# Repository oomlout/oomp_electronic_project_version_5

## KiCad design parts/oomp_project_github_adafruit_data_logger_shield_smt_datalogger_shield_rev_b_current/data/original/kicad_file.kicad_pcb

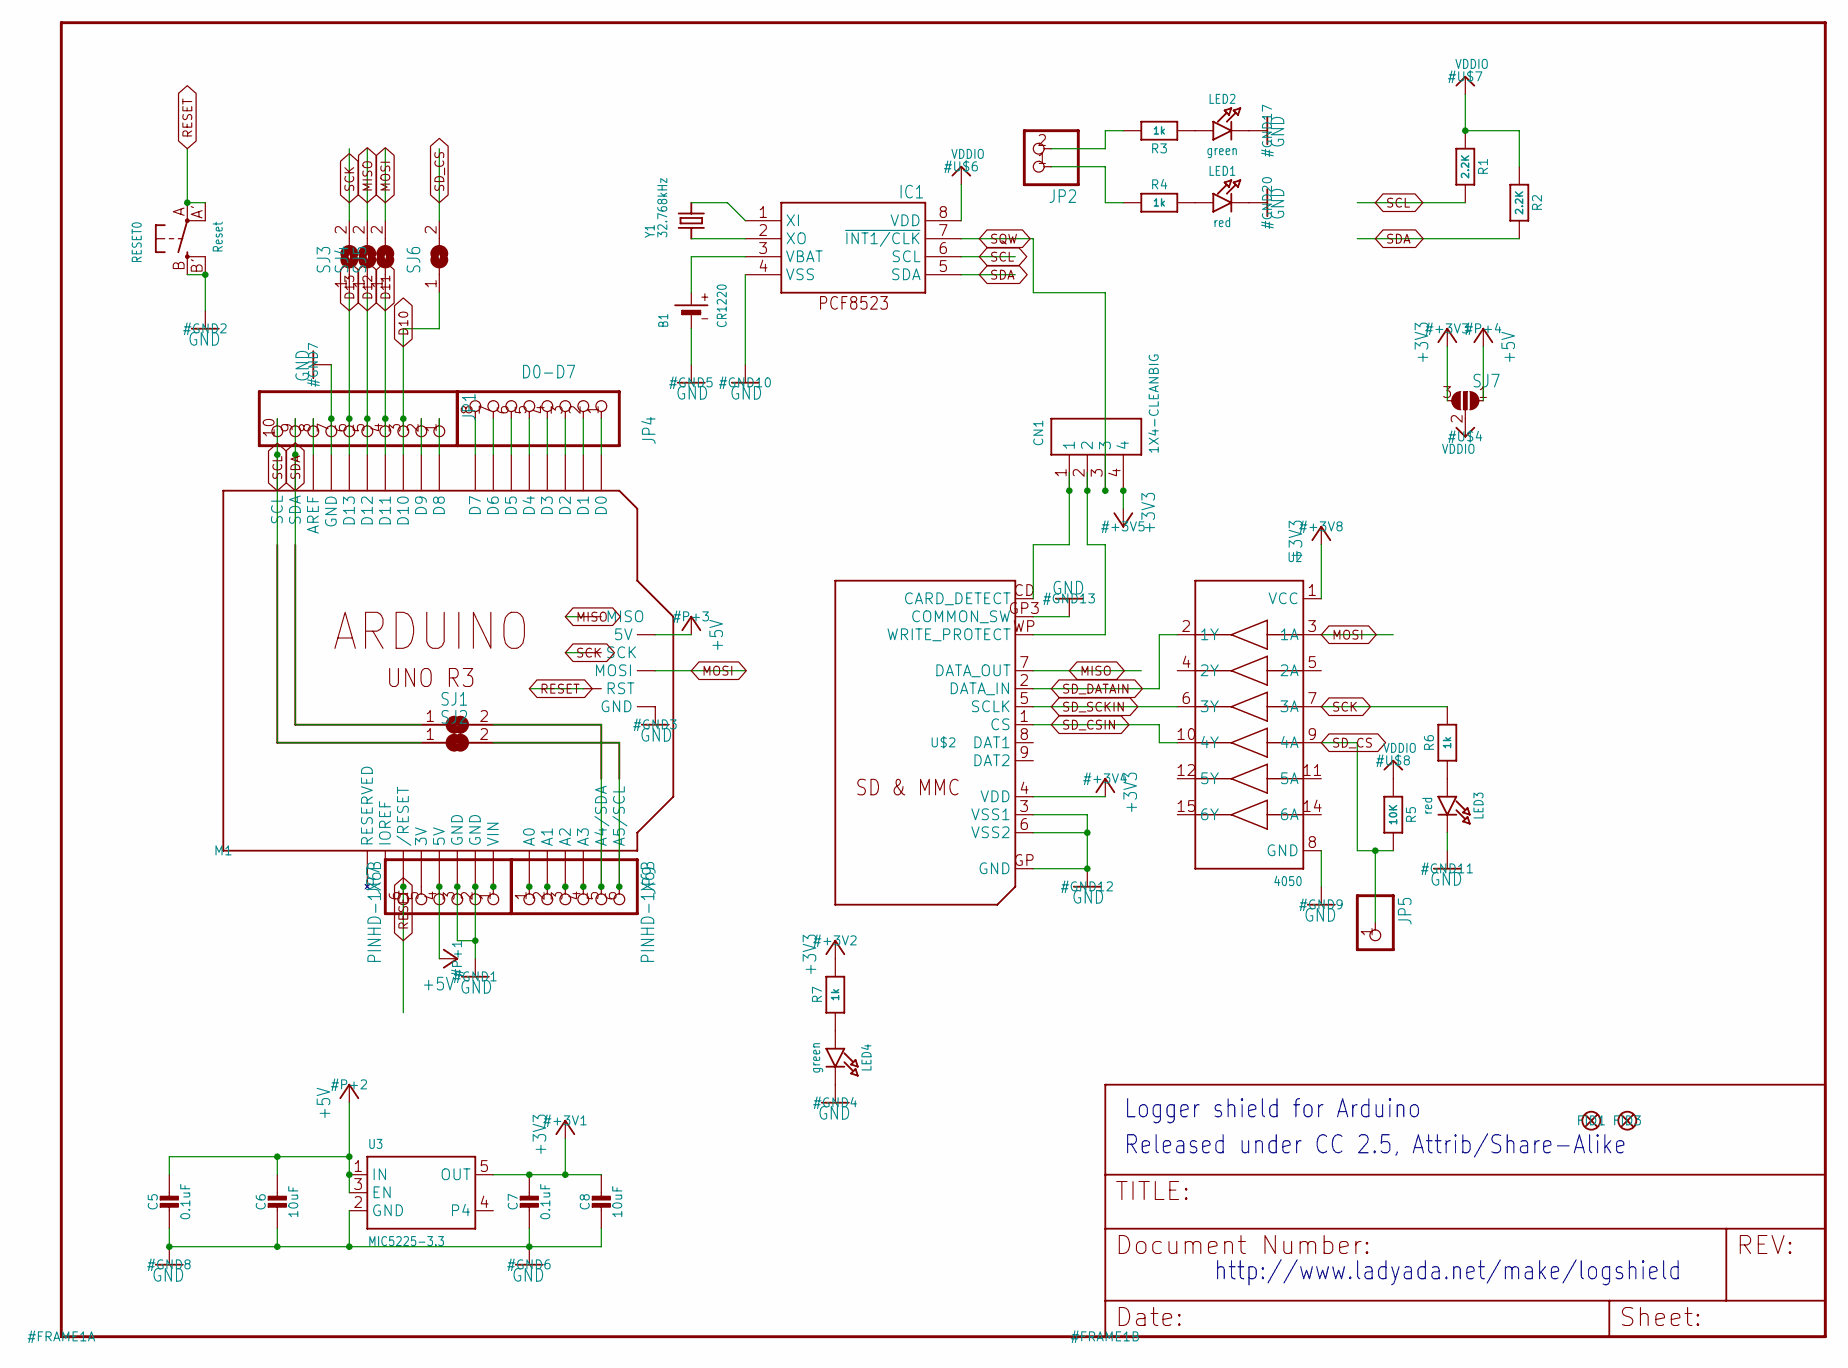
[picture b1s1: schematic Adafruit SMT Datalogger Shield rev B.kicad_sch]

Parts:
B1: CR1220
C5, C7: 0.1uF; 0805-NO
C6, C8: 10uF; 0805-NO
CN1: 1X4-CLEANBIG; 1X04-CLEANBIG
FID1, FID3: FIDUCIAL""; FIDUCIAL_1MM
IC1: RTC_PCF8523T; SOIC8_150MIL
JP1: HEADER-1X1070MIL; 1X10_ROUND70
JP2: HEADER-1X2ROUND; 1X02_ROUND
JP4: D0-D7; 1X08-BIG
JP5: HEADER-1X1ROUND; 1X01_ROUND
JP7, JP9: PINHD-1X6B; 1X06-BIG
LED1, LED3: red; CHIPLED_0805_NOOUTLINE
LED2, LED4: green; CHIPLED_0805_NOOUTLINE
M1: ARDUINO_R3_ICSP; ARDUINOR3_ICSP
R1, R2: 2.2K; 0805-NO
R3, R4, R6, R7: 1k; 0805-NO
R5: 10K; 0805-NO
RESET0: Reset; EVQ-Q2
SJ1, SJ2, SJ3, SJ4, SJ5: SOLDERJUMPER; SOLDERJUMPER_ARROW_NOPASTE
SJ6: SOLDERJUMPERCLOSED; SOLDERJUMPER_CLOSEDWIRE
SJ7: SOLDERJUMPER_2WAY; SOLDERJUMPER_2WAY_OPEN_NOPASTE
U2: 4050; SOIC16
U3: MIC5225-3.3; SOT23-5
U$2: SDMMC06132; 06132
Y1: 32.768kHz; CRYSTAL_8X3.8

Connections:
3.3V: JP7.5, M1.3V
+3V3: C7.1, C8.1, CN1.4, R7.2, SJ7.3, U2.1 (VCC), U3.5 (OUT), U$2.4 (VDD)
+5V: C5.1, C6.1, JP7.4, M1.5V, M1.5V_ICSP (5V), SJ7.1, U3.1 (IN), U3.3 (EN)
A4: JP9.5, M1.A4 (A4/SDA), SJ1.2
A5: JP9.6, M1.A5 (A5/SCL), SJ2.2
D10: JP1.3, M1.D10, SJ6.1
D11: JP1.4, M1.D11, SJ5.1
D12: JP1.5, M1.D12, SJ4.1
D13: JP1.6, M1.D13, SJ3.1
GND: B1.-, C5.2, C6.2, C7.2, C8.2, IC1.4 (VSS), JP1.7, JP7.2, JP7.3, LED1.C, LED2.C, LED3.C, LED4.C, M1.GND, M1.GND@1 (GND), M1.GND@2 (GND), M1.GND@3 (GND), RESET0.B (S), RESET0.B' (S1), U2.8 (GND), U3.2 (GND), U$2.3 (VSS1), U$2.6 (VSS2), U$2.GP (GND), U$2.GP3 (COMMON_SW)
MISO: M1.MISO, SJ4.2, U$2.7 (DATA_OUT)
MOSI: M1.MOSI, SJ5.2, U2.3 (1A)
unnamed: LED1.A, R4.2
unnamed: IC1.2 (XO), Y1.P$1 (1)
unnamed: IC1.1 (XI), Y1.P$4 (2)
unnamed: LED2.A, R3.1
unnamed: LED3.A, R6.1
unnamed: JP7.1, M1.VIN
unnamed: JP2.2, R3.2
unnamed: JP2.1, R4.1
unnamed: JP4.1, M1.D0
unnamed: JP4.2, M1.D1
unnamed: JP4.3, M1.D2
unnamed: JP4.4, M1.D3
unnamed: JP4.5, M1.D4
unnamed: JP4.6, M1.D5
unnamed: JP4.7, M1.D6
unnamed: JP4.8, M1.D7
unnamed: JP1.8, M1.AREF
unnamed: JP1.2, M1.D9
unnamed: JP1.1, M1.D8
unnamed: LED4.A, R7.1
unnamed: JP9.1, M1.A0
unnamed: JP9.2, M1.A1
unnamed: JP9.3, M1.A2
unnamed: JP9.4, M1.A3
RESET: JP7.6, M1.RESET (/RESET), M1.RESET_ICSP (RST), RESET0.A, RESET0.A' (P1)
SCK: M1.SCK, R6.2, SJ3.2, U2.7 (3A)
SCL: IC1.6 (SCL), JP1.10, M1.SCL, R1.2, SJ2.1
SDA: IC1.5 (SDA), JP1.9, M1.SDA, R2.2, SJ1.1
SD_CD: CN1.1, U$2.CD (CARD_DETECT)
SD_CS: JP5.1, R5.2, SJ6.2, U2.9 (4A)
SD_CSIN: U2.10 (4Y), U$2.1 (CS)
SD_DATAIN: U2.2 (1Y), U$2.2 (DATA_IN)
SD_SCKIN: U2.6 (3Y), U$2.5 (SCLK)
SD_WP: CN1.2, U$2.WP (WRITE_PROTECT)
SQW: CN1.3, IC1.7 (~INT1/CLK)
VBAT: B1.+$1 (+), IC1.3 (VBAT)
VDDIO: IC1.8 (VDD), R1.1, R2.1, R5.1, SJ7.2

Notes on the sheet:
http://www.ladyada.net/make/logshield
Released under CC 2.5, Attrib/Share-Alike
Logger shield for Arduino

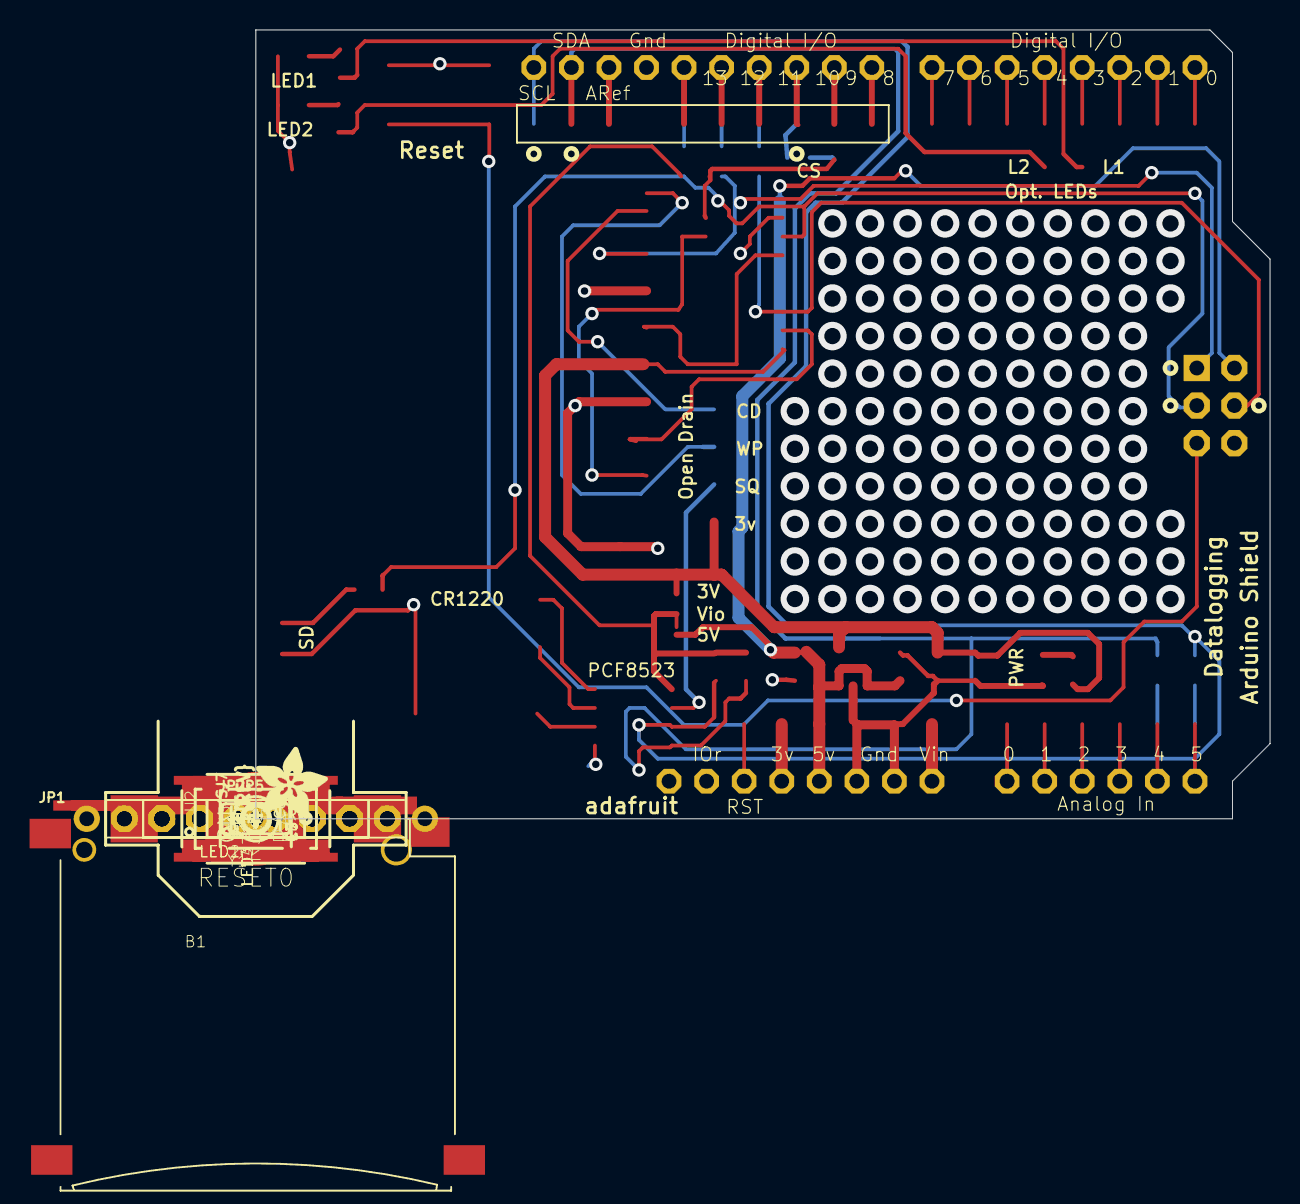
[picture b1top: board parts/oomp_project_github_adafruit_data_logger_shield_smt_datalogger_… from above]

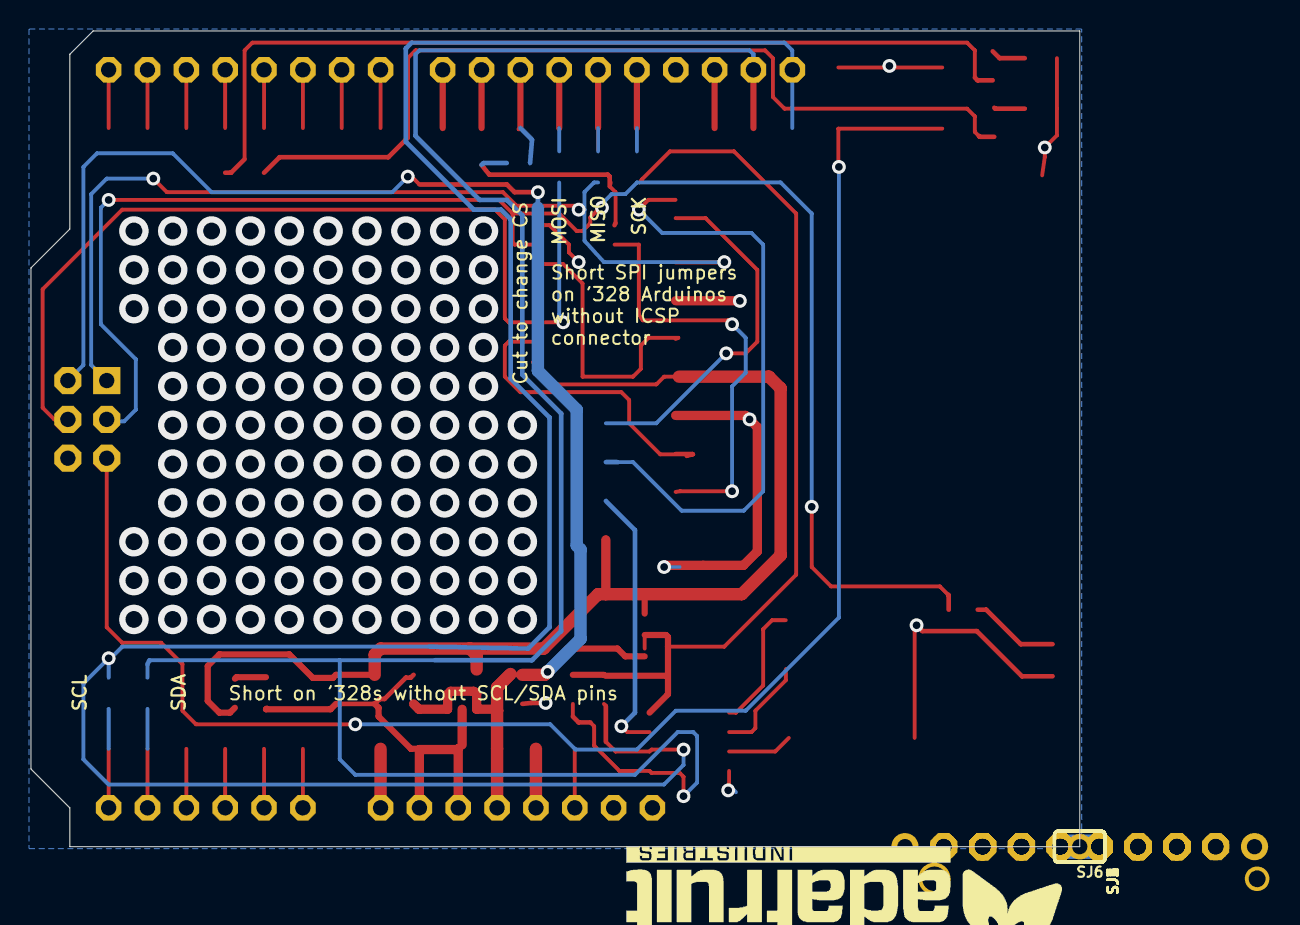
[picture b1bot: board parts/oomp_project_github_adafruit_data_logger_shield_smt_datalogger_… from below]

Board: 2 copper layers, 68.6 x 53.3 mm, 42 parts (7 on the bottom side), 49 nets.

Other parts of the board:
U$1: ADAFRUIT_TEXT_30MM
U$3: PCBFEAT-REV-040
U$5: ADAFRUIT_5MM

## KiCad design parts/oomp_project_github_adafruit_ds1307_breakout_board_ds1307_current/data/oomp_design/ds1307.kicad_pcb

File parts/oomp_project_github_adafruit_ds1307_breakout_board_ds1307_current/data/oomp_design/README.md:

# OOMP KiCad design copy

Open `ds1307.kicad_pro` (or the `.kicad_pcb` / `.kicad_sch`) in KiCad. Local OOMP libraries are under `libraries/`. Original inputs are preserved in [../original/](../original/).

Only verified unchanged installed KiCad defaults were renamed. Modified, custom, unmatched and unavailable items remain unchanged. Soldering variants are never swapped during conversion. Existing pad coordinates, nets and UUIDs are preserved.

See [conversion_report.yaml](conversion_report.yaml) for every conversion and skip. Copy this directory before editing; regeneration refuses to overwrite edited design files.

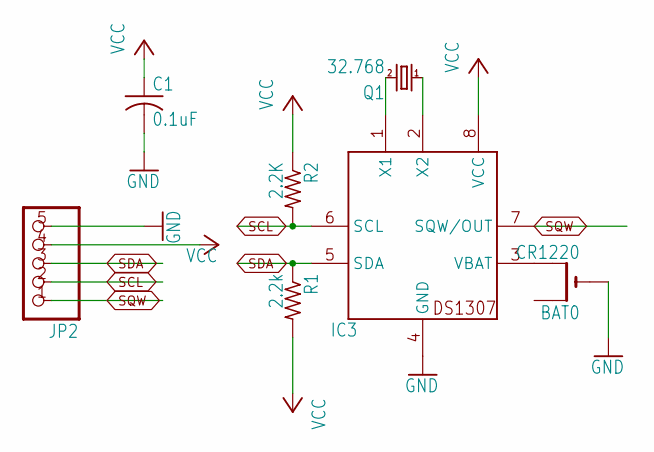
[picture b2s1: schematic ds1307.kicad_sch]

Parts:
BAT0: CR1220; CR1220-THM
C1: 0.1uF; C025-025X050
IC3: DS1307; DIL08
JP2: PINHD-1X5; 1X05
Q1: 32.768; TC38H
R1: 2.2k; 0207_10
R2: 2.2K; 0207_10

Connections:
GND: BAT0.-, C1.2, IC3.4 (GND), JP2.5
unnamed: IC3.1 (X1), Q1.2
unnamed: IC3.2 (X2), Q1.1
unnamed: BAT0.+2 (+1), IC3.3 (VBAT)
SCL: IC3.6 (SCL), JP2.2, R2.2
SDA: IC3.5 (SDA), JP2.3, R1.1
SQW: IC3.7 (SQW/OUT), JP2.1
VCC: C1.1, IC3.8 (VCC), JP2.4, R1.2, R2.1

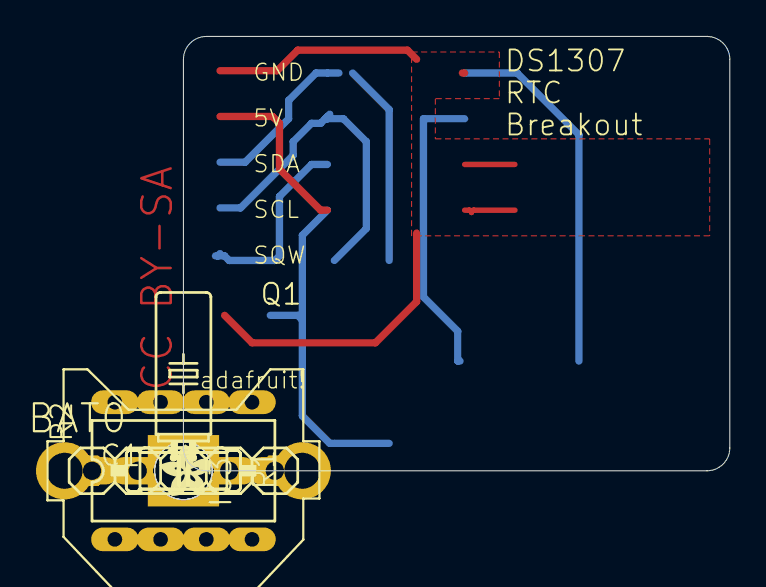
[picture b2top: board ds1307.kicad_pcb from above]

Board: 16 copper layers, 30.4 x 24.1 mm, 10 parts (0 on the bottom side), 8 nets.

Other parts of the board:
U$1: ADAFRUIT200MIL
UNK_HOLE_0: dummyfp0
UNK_HOLE_1: dummyfp1

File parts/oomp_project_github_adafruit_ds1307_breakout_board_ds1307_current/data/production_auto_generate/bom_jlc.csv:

Comment,Designator,Footprint,LCSC Part #
,JP2,ds1307-import-fps:1X05,C42431835
,U$1,ds1307-import-fps:ADAFRUIT200MIL,
0.1uF,C1,ds1307-import-fps:C025-025X050,
2.2k,R1,ds1307-import-fps:0207_10,
2.2K,R2,ds1307-import-fps:0207_10,
32.768,Q1,ds1307-import-fps:TC38H,
CR1220,BAT0,ds1307-import-fps:CR1220-THM,
DS1307,IC3,ds1307-import-fps:DIL08,

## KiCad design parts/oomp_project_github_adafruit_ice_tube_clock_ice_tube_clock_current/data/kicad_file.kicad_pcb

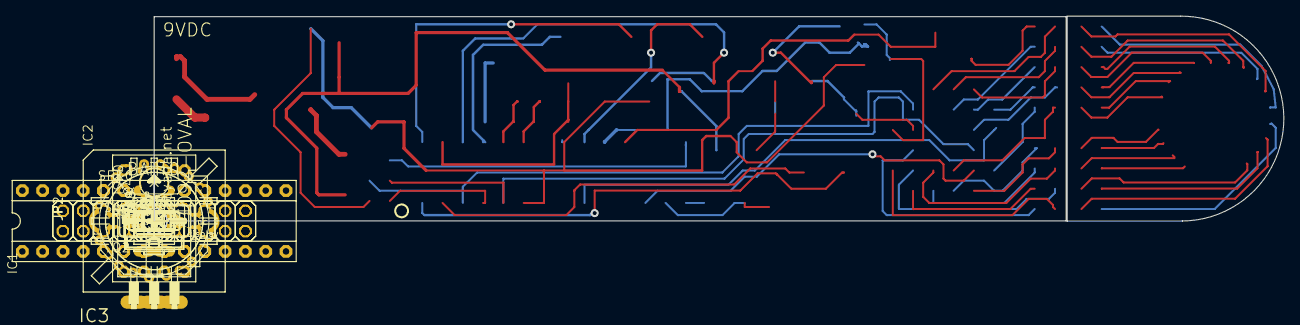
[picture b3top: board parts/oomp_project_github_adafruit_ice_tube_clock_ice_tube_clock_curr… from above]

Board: 16 copper layers, 141.5 x 25.7 mm, 33 parts (0 on the bottom side), 7 nets.

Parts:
BATT0: CR1220; CR1220-THM
C7: 47uF/25V; E2,5-6
C8, C9: 22pf; C025-025X050
C10: 0.1uF; C025-024X044
CT0, CT1: 1X01
D2, D4: 1N5817; DO41-10
D5: 60V zener; DO41Z10
DIS1: IV18
F1: FUSETE5; TE5
IC1: ATMEGA168V; DIL28_3
IC2: MAX6921; PLCC-S28
IC3: 7805T; TO220H
ISP0: ISP; 2X03
JP1: female; 2X10
JP2: male; 2X10
Q1: 32.768 khz; TC26V
Q2: IRFD110; DIL04
Q4: PFETZVP3306; ladyada.net
R1: 270k; 0207_10
R2: 100k; 0207_10
R3: 22; 0207_10
R4: 1.0 K; 0207_5V
R5: 10k; 0207_5V
S1, S2, S3: B3F-31XX
SPK0: PS1240; PS12
SW1: ALARM; OS102011MA1Q
UNK_HOLE_0: dummyfp0
UNK_HOLE_1: dummyfp1

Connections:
+9V: C7.-, D5.C, DIS1.17, IC1.2, ISP0.2, R2.2
+UB: IC2.2, Q1.1, S1.2, S2.1
BATTSNS: JP2.2, S3.1
unnamed: DIS1.6, IC2.1, SW1.2, SW1.MT2
unnamed: BATT0.-, C9.1
unnamed: F1.1, R5.1
VCC: D4.C, JP1.2, JP2.1, R1.1, R3.2

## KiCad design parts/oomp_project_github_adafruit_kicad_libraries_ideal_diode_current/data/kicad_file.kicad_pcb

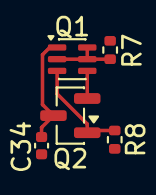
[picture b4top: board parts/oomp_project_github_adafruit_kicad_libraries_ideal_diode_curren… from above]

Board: 4 copper layers, 5 parts (0 on the bottom side), 5 nets.

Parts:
C34: 1uF/16V(10%); C_0402_1005Metric
Q1: MBT3906DW1; SOT-363_SC-70-6
Q2: AO3401A; SOT-23
R7: 10K(1%); R_0402_1005Metric
R8: 51K(1%); R_0402_1005Metric

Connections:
/FS_VBUS: C34.1, Q1.1 (E1), Q2.3 (D)
GND: C34.2, R7.2, R8.2
unnamed: Q1.2 (B1), Q1.5 (B2), Q1.6 (C1), R7.1
unnamed: Q1.3 (C2), Q2.1 (G), R8.1
VBUS: Q1.4 (E2), Q2.2 (S)

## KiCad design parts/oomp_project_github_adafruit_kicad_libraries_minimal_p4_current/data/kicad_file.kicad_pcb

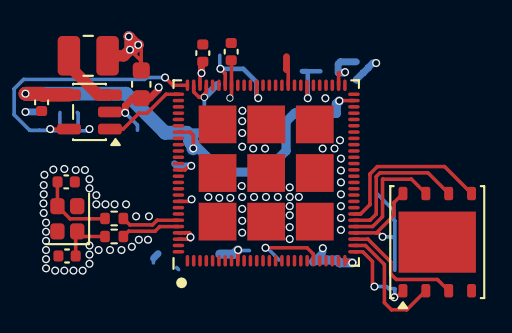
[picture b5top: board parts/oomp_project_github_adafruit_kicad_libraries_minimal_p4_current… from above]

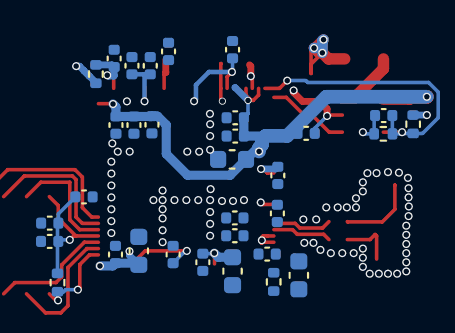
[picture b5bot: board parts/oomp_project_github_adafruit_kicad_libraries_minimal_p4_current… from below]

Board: 4 copper layers, 45 parts (32 on the bottom side), 20 nets.

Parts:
C1, C42: 4.7uF; C_0402_1005Metric
C2: 22pF; C_0402_1005Metric
C3: 22uF; C_0603_1608Metric
C4, C5: 12pF; C_0402_1005Metric
C6, C7, C8, C9, C12, C13, C15, C16, C21, C23, C24, C25, C26, C31, C32, C33, C40: 0.1uF; C_0402_1005Metric
C11, C14, C20, C28: 10uF; C_0603_1608Metric
C17, C18, C27, C29, C30: 1uF; C_0402_1005Metric
C41: 10nF; C_0402_1005Metric
L1: 2.2uH; L_1008_2520Metric
R1, R2: 499k; R_0402_1005Metric
R3, R4, R39: 0; R_0402_1005Metric
R28, R200: 10k; R_0402_1005Metric
U1: TLV62569DBV; SOT-23-5
U2: ESP32-P4
U3: W25Q128JVS; WSON-8-1EP_6x5mm_P1.27mm_EP3.4x4.3mm
Y1: 40MHz(+-10 ppm) C501798; Crystal_SMD_2016-4Pin_2.0x1.6mm

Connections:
+3.3V: C1.1, C6.1, C7.1, C9.1, C11.1, C12.1, C13.1, C14.1, C16.1, C20.1, C21.1, C23.1, C24.1, C40.1, C41.1, C42.1, R200.2, U1.4 (VIN), U2.9 (VDD_LP), U2.21 (VDD_IO_0), U2.51 (VDD_USBPHY), U2.62 (VDD_IO_4), U2.75 (VDD_LDO), U2.77 (VDD_DCDCC), U2.85 (VDD_IO_5), U2.96 (VDD_IO_6), U2.101 (VDD_ANA), U2.102 (VDD_BAT)
/Minimal P4 V3/EN_DCDC: U1.1 (EN), U2.79 (EN_DCDC)
/Minimal P4 V3/FB_DCDC: C2.2, R1.1, R2.2, U1.5 (FB), U2.78 (FB_DCDC)
/Minimal P4 V3/FLASH_CK: U2.32 (FLASH_CK), U3.6 (CLK)
/Minimal P4 V3/FLASH_CS: R28.1, U2.27 (FLASH_CS), U3.1 (~CS)
/Minimal P4 V3/FLASH_D: U2.33 (FLASH_D), U3.5 (DI/IO_{0})
/Minimal P4 V3/FLASH_HOLD: U2.31 (FLASH_HOLD), U3.7 (~HOLD/~RESET/IO_{3})
/Minimal P4 V3/FLASH_Q: U2.28 (FLASH_Q), U3.2 (DO/IO_{1})
/Minimal P4 V3/FLASH_WP: U2.29 (FLASH_WP), U3.3 (~WP/IO_{2})
/Minimal P4 V3/VDDO_PSRAM: C18.1, C26.1, C27.1, U2.59 (VDD_PSRAM_0), U2.67 (VDD_PSRAM_1), U2.72 (VDDO_PSRAM)
/Minimal P4 V3/VDD_FLASH: C17.1, C30.1, C31.1, C32.1, R28.2, U2.30 (VDD_FLASH_IO), U2.71 (VDDO_FLASH), U3.8 (VCC)
/Minimal P4 V3/VDD_HP: C2.1, C3.1, C8.1, C15.1, C28.1, C29.1, L1.2, R1.2, R39.1, U2.26 (VDD_HP_0), U2.76 (VDD_HP_2), U2.91 (VDD_HP_3)
/RESET: C33.1, R200.1, U2.103 (CHIP_PU)
GND: C1.2, C3.2, C4.1, C5.2, C6.2, C7.2, C8.2, C9.2, C11.2, C12.2, C13.2, C14.2, C15.2, C16.2, C17.2, C18.2, C20.2, C21.2, C23.2, C24.2, C25.2, C26.2, C27.2, C28.2, C29.2, C30.2, C31.2, C32.2, C33.2, C40.2, C41.2, C42.2, R2.1, U1.2 (GND), U2.105 (GND), U3.4 (GND), Y1.2 (G), Y1.4 (G)
unnamed: C4.2, R3.2, Y1.1
unnamed: C5.1, R4.2, Y1.3
unnamed: L1.1, U1.3 (SW)
unnamed: C25.1, R39.2, U2.54 (VDD_HP_1)
unnamed: R4.1, U2.99 (XTAL_N)
unnamed: R3.1, U2.100 (XTAL_P)

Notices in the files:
parts/oomp_project_github_adafruit_ds1307_breakout_board_ds1307_current/data/oomp_design/ds1307.kicad_pcb:
CC BY-SA
